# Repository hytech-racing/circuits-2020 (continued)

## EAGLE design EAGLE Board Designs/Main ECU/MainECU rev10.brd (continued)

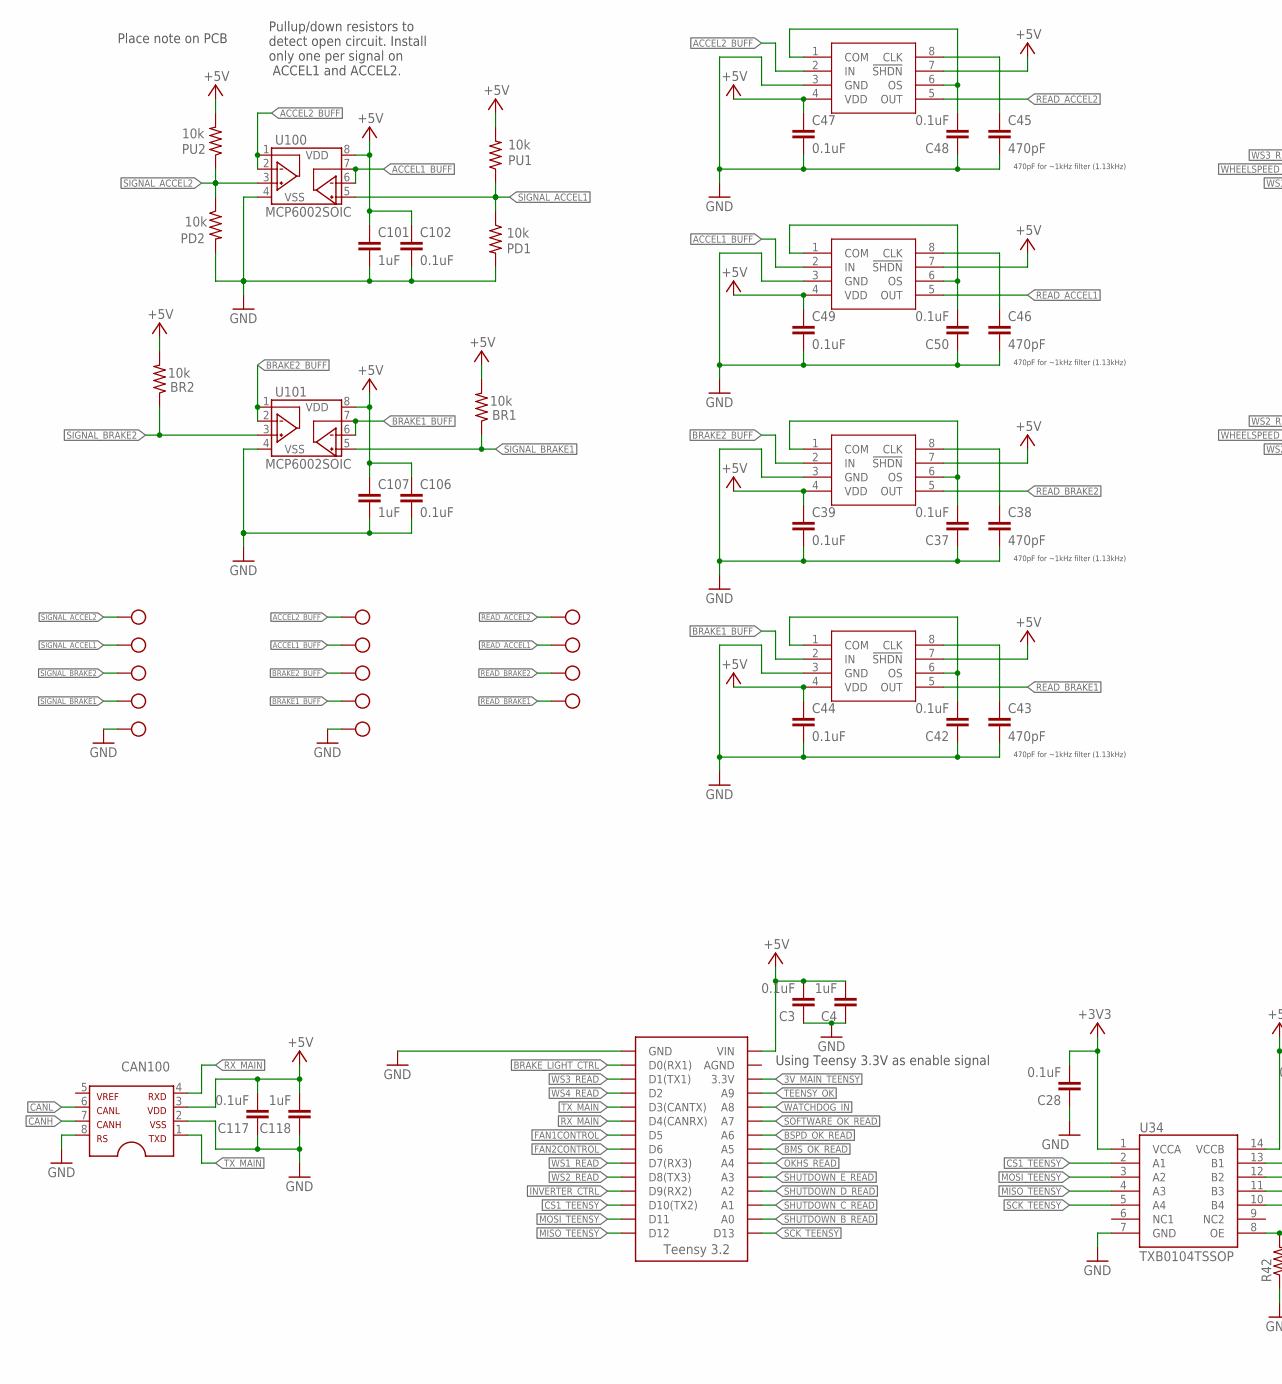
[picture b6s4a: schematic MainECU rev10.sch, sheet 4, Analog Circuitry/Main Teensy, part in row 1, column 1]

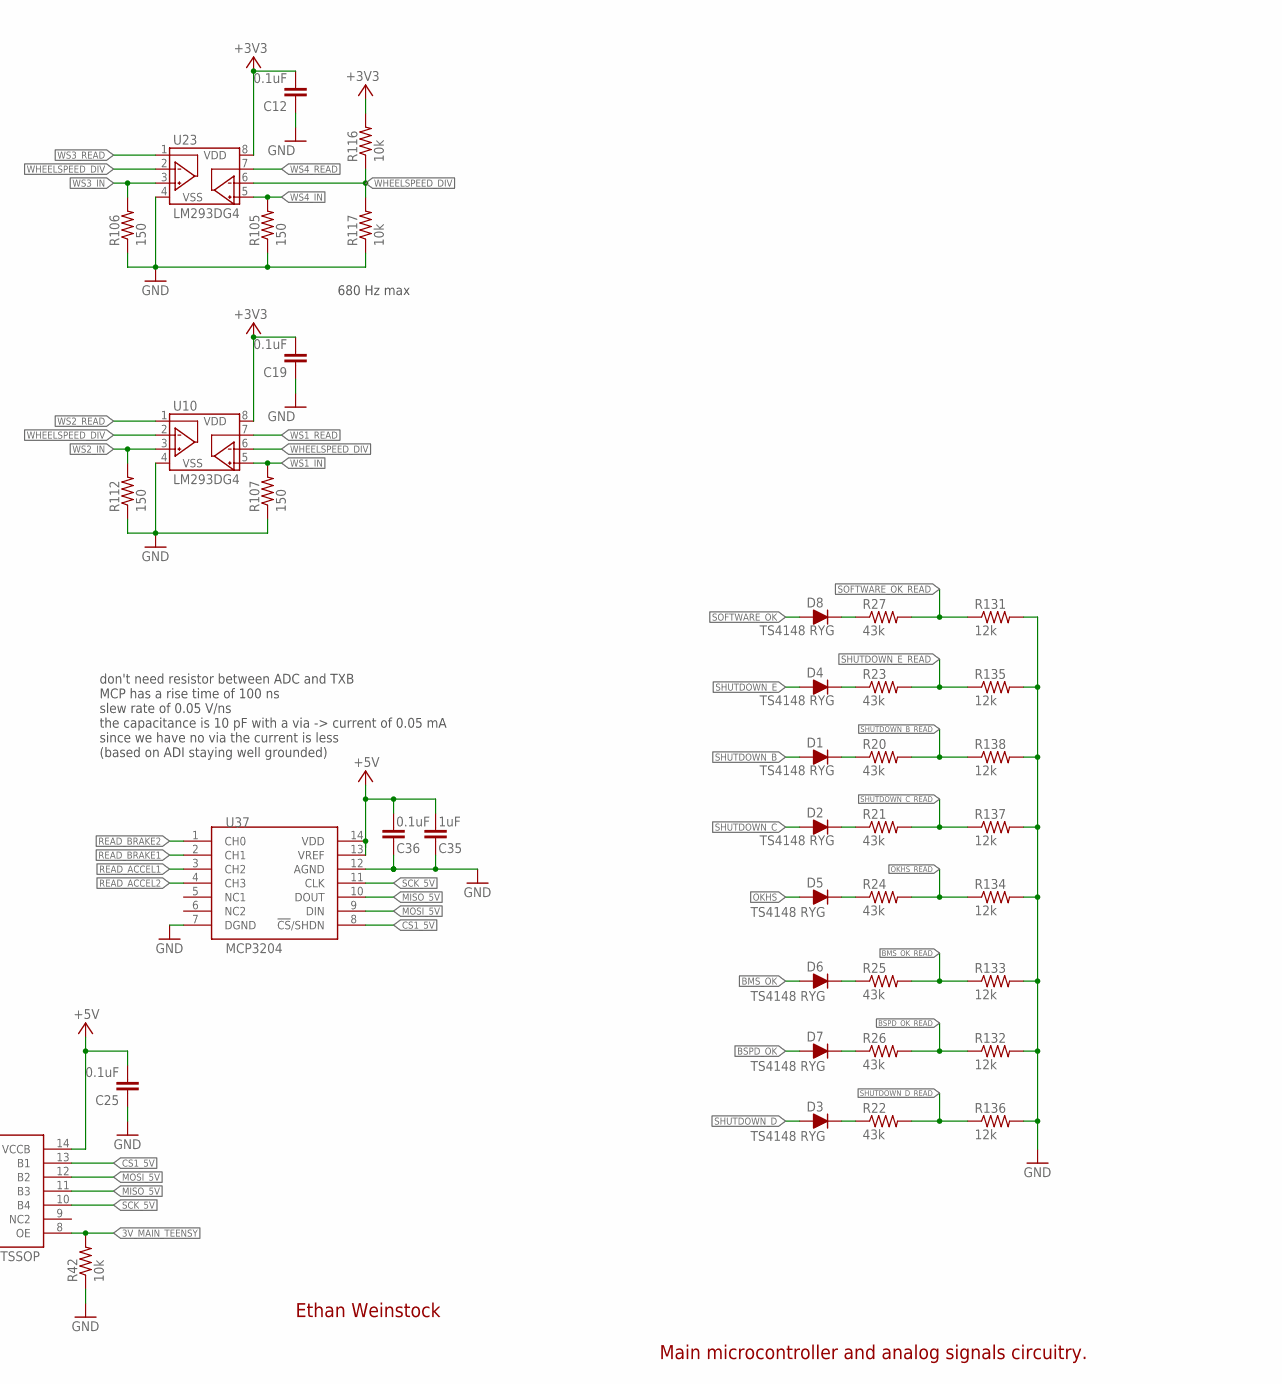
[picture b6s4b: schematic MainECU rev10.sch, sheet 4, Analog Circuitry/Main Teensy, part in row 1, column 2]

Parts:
ACCEL1_BUFF_TEST: 12V_TEST; MICRO_MINIATURE
ACCEL2_BUFF_TEST: TEST_POINTMICRO_MINIATURE; MICRO_MINIATURE
BR1, BR2: 10k; 0603-RES
BRAKE1_BUFF_TEST, BRAKE2_BUFF_TEST: TEST_POINTMICRO_MINIATURE; MICRO_MINIATURE
C3, C12, C19, C25, C28, C36, C37, C39, C42, C44, C47, C48, C49, C50, C102, C106, C117: 0.1uF; 0603-CAP
C4, C35, C101, C107, C118: 1uF; 0603-CAP
C38, C43, C45, C46: 470pF; 0603-CAP
CAN100: MCP2551; SOIC-08
D1, D2, D3, D4, D5, D6, D7, D8: TS4148 RYG; 0805_D
PD1, PD2: 10k; 0603-RES
PU1, PU2: 10k; 0603-RES
R20, R21, R22, R23, R24, R25, R26, R27: 43k; 0603-RES
R42, R116, R117: 10k; 0603-RES
R105, R106, R107, R112: 150; 0603-RES
R131, R132, R133, R134, R135, R136, R137, R138: 12k; 0603-RES
READ_ACCEL1_TEST: 12V_TEST; MICRO_MINIATURE
READ_ACCEL2_TEST: TEST_POINTMICRO_MINIATURE; MICRO_MINIATURE
READ_BRAKE1_TEST, READ_BRAKE2_TEST: TEST_POINTMICRO_MINIATURE; MICRO_MINIATURE
SIGNAL_ACCEL1_TEST: 12V_TEST; MICRO_MINIATURE
SIGNAL_ACCEL2_TEST: TEST_POINTMICRO_MINIATURE; MICRO_MINIATURE
SIGNAL_BRAKE1_TEST, SIGNAL_BRAKE2_TEST: TEST_POINTMICRO_MINIATURE; MICRO_MINIATURE
SIGNAL_GND: TEST_POINTMICRO_MINIATURE; MICRO_MINIATURE
U5: TEENSY_3.2_SIMPLE
U10, U23: LM293DG4; SOIC-08
U34: TXB0104TSSOP; TSSOP-14
U37: MCP3204; SO14
U38, U39, U44, U45: MAX7480; SOIC-08
U46: TEST_POINTMICRO_MINIATURE; MICRO_MINIATURE
U100, U101: MCP6002SOIC; SOIC-08

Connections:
3V_MAIN_TEENSY: R42.2, U5.3.3V, U34.8 (OE)
+3V3: C12.2, C19.2, C28.2, R116.2, U10.8 (VDD), U23.8 (VDD), U34.1 (VCCA); also elsewhere on the board
+5V: BR1.2, BR2.2, C3.2, C4.2, C25.2, C35.2, C36.2, C39.1, C44.1, C47.1, C49.1, C101.1, C102.1, C106.1, C107.1, C117.2, C118.2, CAN100.3, PU1.2, PU2.2, U5.VIN, U34.14 (VCCB), U37.13 (VREF), U37.14 (VDD), U38.4 (VDD), U38.7 (!SHDN), U39.4 (VDD), U39.7 (!SHDN), U44.4 (VDD), U44.7 (!SHDN), U45.4 (VDD), U45.7 (!SHDN), U100.8 (VDD), U101.8 (VDD); also elsewhere on the board
ACCEL1_BUFF: ACCEL2_BUFF_TEST.P$1, U45.2 (IN), U100.6 (VINB-), U100.7 (VOUTB)
ACCEL2_BUFF: ACCEL1_BUFF_TEST.P$1, U44.2 (IN), U100.1 (VOUTA), U100.2 (VINA-)
BMS_OK: D6.A; also elsewhere on the board
BMS_OK_READ: R25.2, R133.1, U5.A5
BRAKE1_BUFF: BRAKE2_BUFF_TEST.P$1, U39.2 (IN), U101.6 (VINB-), U101.7 (VOUTB)
BRAKE2_BUFF: BRAKE1_BUFF_TEST.P$1, U38.2 (IN), U101.1 (VOUTA), U101.2 (VINA-)
BRAKE_LIGHT_CTRL: U5.D0(RX1); also elsewhere on the board
BSPD_OK: D7.A; also elsewhere on the board
BSPD_OK_READ: R26.2, R132.1, U5.A6
CANH: CAN100.7; also elsewhere on the board
CANL: CAN100.6; also elsewhere on the board
CS1_5V: U34.13 (B1), U37.8 (!CS!/SHDN)
CS1_TEENSY: U5.D10(TX2), U34.2 (A1)
FAN1CONTROL: U5.D5; also elsewhere on the board
FAN2CONTROL: U5.D6; also elsewhere on the board
GND: C3.1, C4.1, C12.1, C19.1, C25.1, C28.1, C35.1, C36.1, C37.1, C38.2, C39.2, C42.1, C43.2, C44.2, C45.2, C46.2, C47.2, C48.1, C49.2, C50.1, C101.2, C102.2, C106.2, C107.2, C117.1, C118.1, CAN100.2, CAN100.8, PD1.2, PD2.2, R42.1, R105.1, R106.1, R107.1, R112.1, R117.1, R131.2, R132.2, R133.2, R134.2, R135.2, R136.2, R137.2, R138.2, SIGNAL_GND.P$1, U5.GND, U10.4 (VSS), U23.4 (VSS), U34.7 (GND), U37.7 (DGND), U37.12 (AGND), U38.3 (GND), U39.3 (GND), U44.3 (GND), U45.3 (GND), U46.P$1, U100.4 (VSS), U101.4 (VSS); also elsewhere on the board
INVERTER_CTRL: U5.D9(RX2); also elsewhere on the board
MISO_5V: U34.11 (B3), U37.10 (DOUT)
MISO_TEENSY: U5.D12, U34.4 (A3)
MOSI_5V: U34.12 (B2), U37.9 (DIN)
MOSI_TEENSY: U5.D11, U34.3 (A2)
unnamed: C43.1, U39.8 (CLK)
unnamed: C42.2, U39.1 (COM), U39.6 (OS)
unnamed: D4.C, R23.1
unnamed: D8.C, R27.1
unnamed: D5.C, R24.1
unnamed: D6.C, R25.1
unnamed: D3.C, R22.1
unnamed: D1.C, R20.1
unnamed: D2.C, R21.1
unnamed: D7.C, R26.1
unnamed: C45.1, U44.8 (CLK)
unnamed: C46.1, U45.8 (CLK)
unnamed: C48.2, U44.1 (COM), U44.6 (OS)
unnamed: C38.1, U38.8 (CLK)
unnamed: C37.2, U38.1 (COM), U38.6 (OS)
unnamed: C50.2, U45.1 (COM), U45.6 (OS)
OKHS: D5.A; also elsewhere on the board
OKHS_READ: R24.2, R134.1, U5.A4
READ_ACCEL1: READ_ACCEL2_TEST.P$1, U37.3 (CH2), U45.5 (OUT)
READ_ACCEL2: READ_ACCEL1_TEST.P$1, U37.4 (CH3), U44.5 (OUT)
READ_BRAKE1: READ_BRAKE2_TEST.P$1, U37.2 (CH1), U39.5 (OUT)
READ_BRAKE2: READ_BRAKE1_TEST.P$1, U37.1 (CH0), U38.5 (OUT)
RX_MAIN: CAN100.4, U5.D4(CANRX)
SCK_5V: U34.10 (B4), U37.11 (CLK)
SCK_TEENSY: U5.D13, U34.5 (A4)
SHUTDOWN_B: D1.A; also elsewhere on the board
SHUTDOWN_B_READ: R20.2, R138.1, U5.A0
SHUTDOWN_C: D2.A; also elsewhere on the board
SHUTDOWN_C_READ: R21.2, R137.1, U5.A1
SHUTDOWN_D: D3.A; also elsewhere on the board
SHUTDOWN_D_READ: R22.2, R136.1, U5.A2
SHUTDOWN_E: D4.A; also elsewhere on the board
SHUTDOWN_E_READ: R23.2, R135.1, U5.A3
SIGNAL_ACCEL1: PD1.1, PU1.1, SIGNAL_ACCEL2_TEST.P$1, U100.5 (VINB+); also elsewhere on the board
SIGNAL_ACCEL2: PD2.1, PU2.1, SIGNAL_ACCEL1_TEST.P$1, U100.3 (VINA+); also elsewhere on the board
SIGNAL_BRAKE1: BR1.1, SIGNAL_BRAKE2_TEST.P$1, U101.5 (VINB+); also elsewhere on the board
SIGNAL_BRAKE2: BR2.1, SIGNAL_BRAKE1_TEST.P$1, U101.3 (VINA+); also elsewhere on the board
SOFTWARE_OK: D8.A; also elsewhere on the board
SOFTWARE_OK_READ: R27.2, R131.1, U5.A7
TEENSY_OK: U5.A9; also elsewhere on the board
TX_MAIN: CAN100.1, U5.D3(CANTX)
WATCHDOG_IN: U5.A8; also elsewhere on the board
WHEELSPEED_DIV: R116.1, R117.2, U10.2 (VINA-), U10.6 (VINB-), U23.2 (VINA-), U23.6 (VINB-)
WS1_IN: R107.2, U10.5 (VINB+); also elsewhere on the board
WS1_READ: U5.D7(RX3), U10.7 (VOUTB)
WS2_IN: R112.2, U10.3 (VINA+); also elsewhere on the board
WS2_READ: U5.D8(TX3), U10.1 (VOUTA)
WS3_IN: R106.2, U23.3 (VINA+); also elsewhere on the board
WS3_READ: U5.D1(TX1), U23.1 (VOUTA)
WS4_IN: R105.2, U23.5 (VINB+); also elsewhere on the board
WS4_READ: U5.D2, U23.7 (VOUTB)

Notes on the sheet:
Pullup/down resistors to detect open circuit. Install only one per signal on ACCEL1 and ACCEL2.
470pF for ~1kHz filter (1.13kHz)
Ethan Weinstock
Main microcontroller and analog signals circuitry.
Place note on PCB
Using Teensy 3.3V as enable signal
680 Hz max
don't need resistor between ADC and TXB MCP has a rise time of 100 ns slew rate of 0.05 V/ns the capacitance is 10 pF with a via -> current of 0.05 mA since we have no via the current is less (based on ADI staying well grounded)

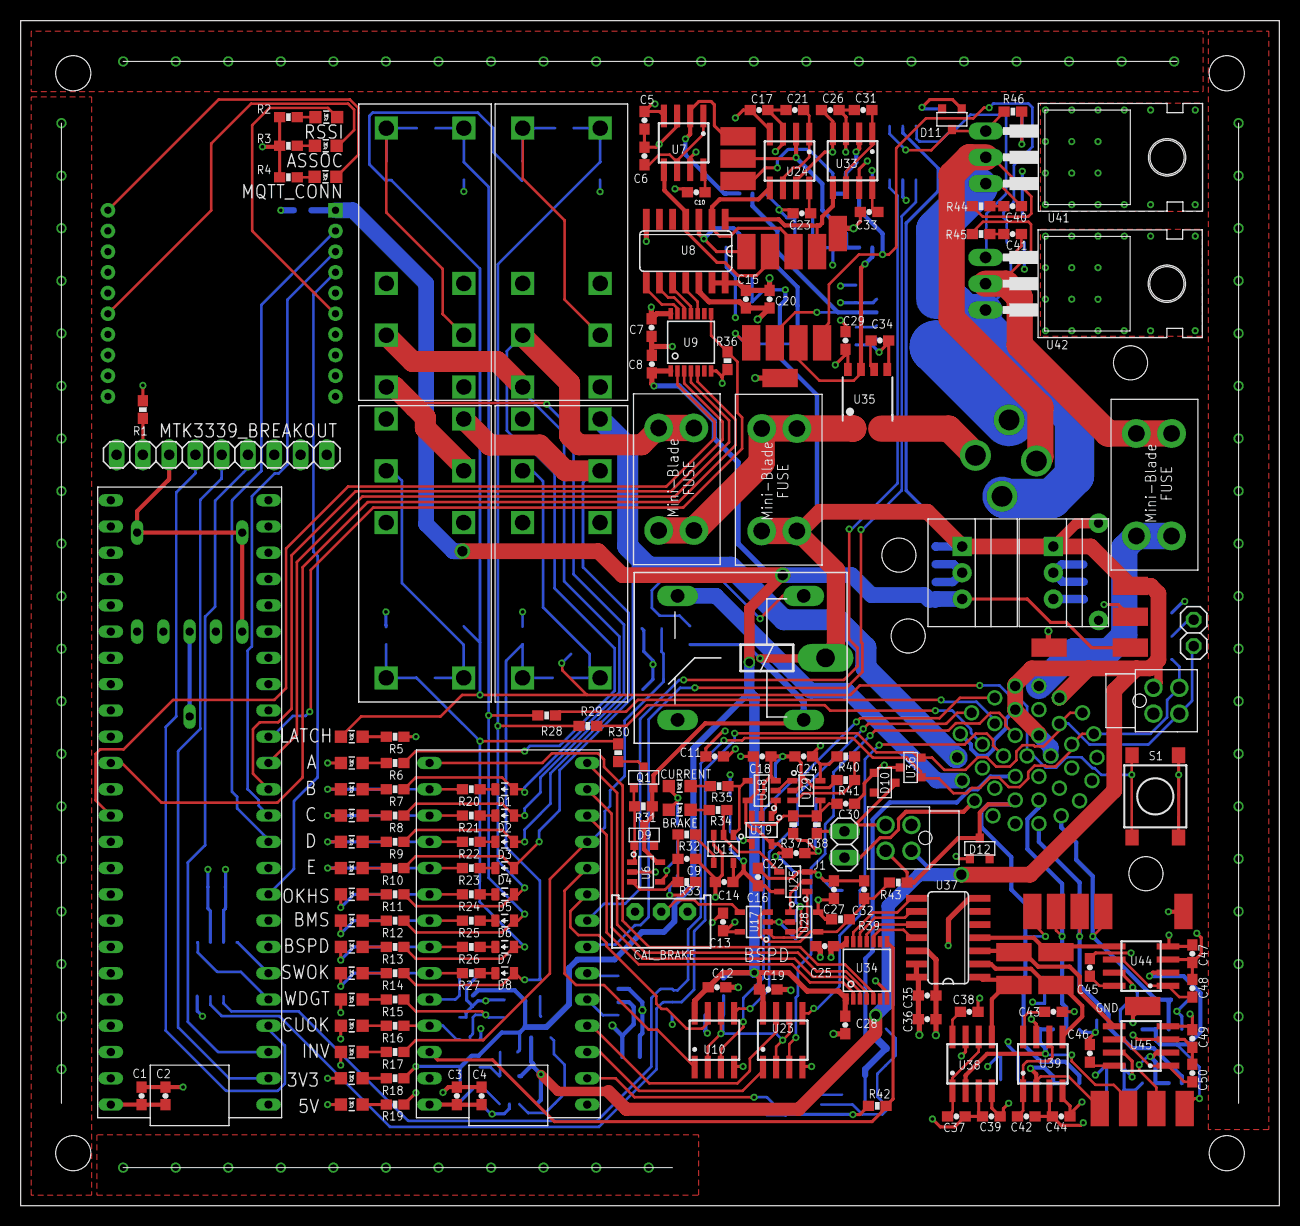
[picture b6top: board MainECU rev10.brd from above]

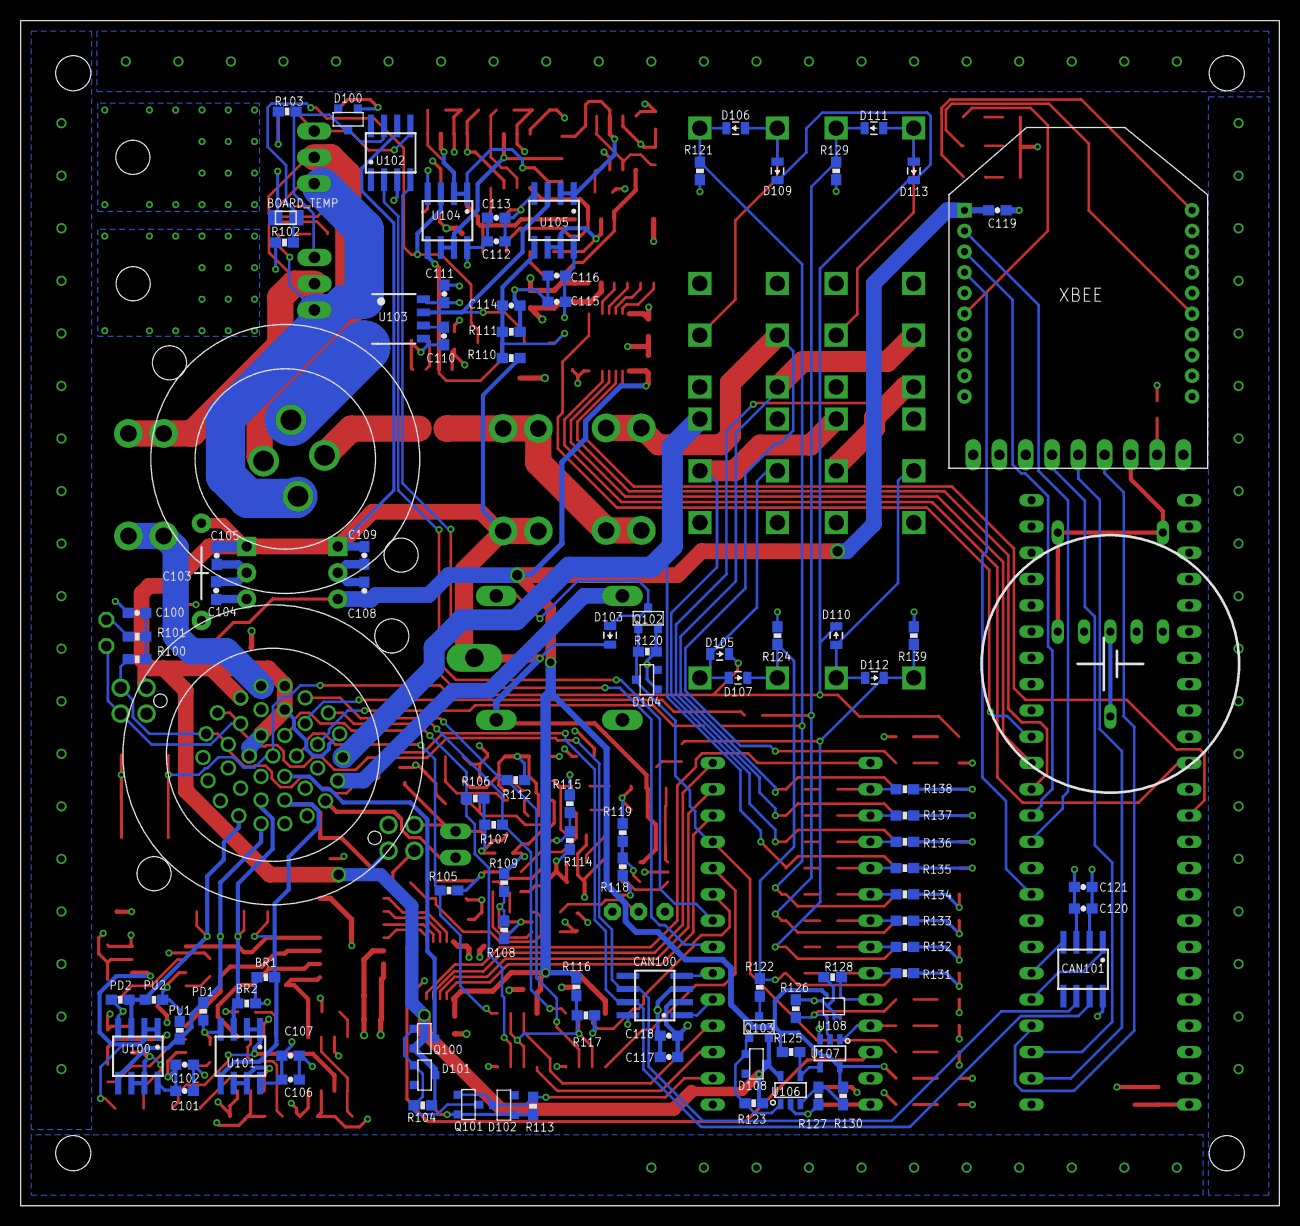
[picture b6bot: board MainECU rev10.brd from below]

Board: 4 copper layers, 121.7 x 114.6 mm, 310 parts (102 on the bottom side), 186 nets.

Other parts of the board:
U$1, U$2, U$3, U$4: M3_MOUNTING

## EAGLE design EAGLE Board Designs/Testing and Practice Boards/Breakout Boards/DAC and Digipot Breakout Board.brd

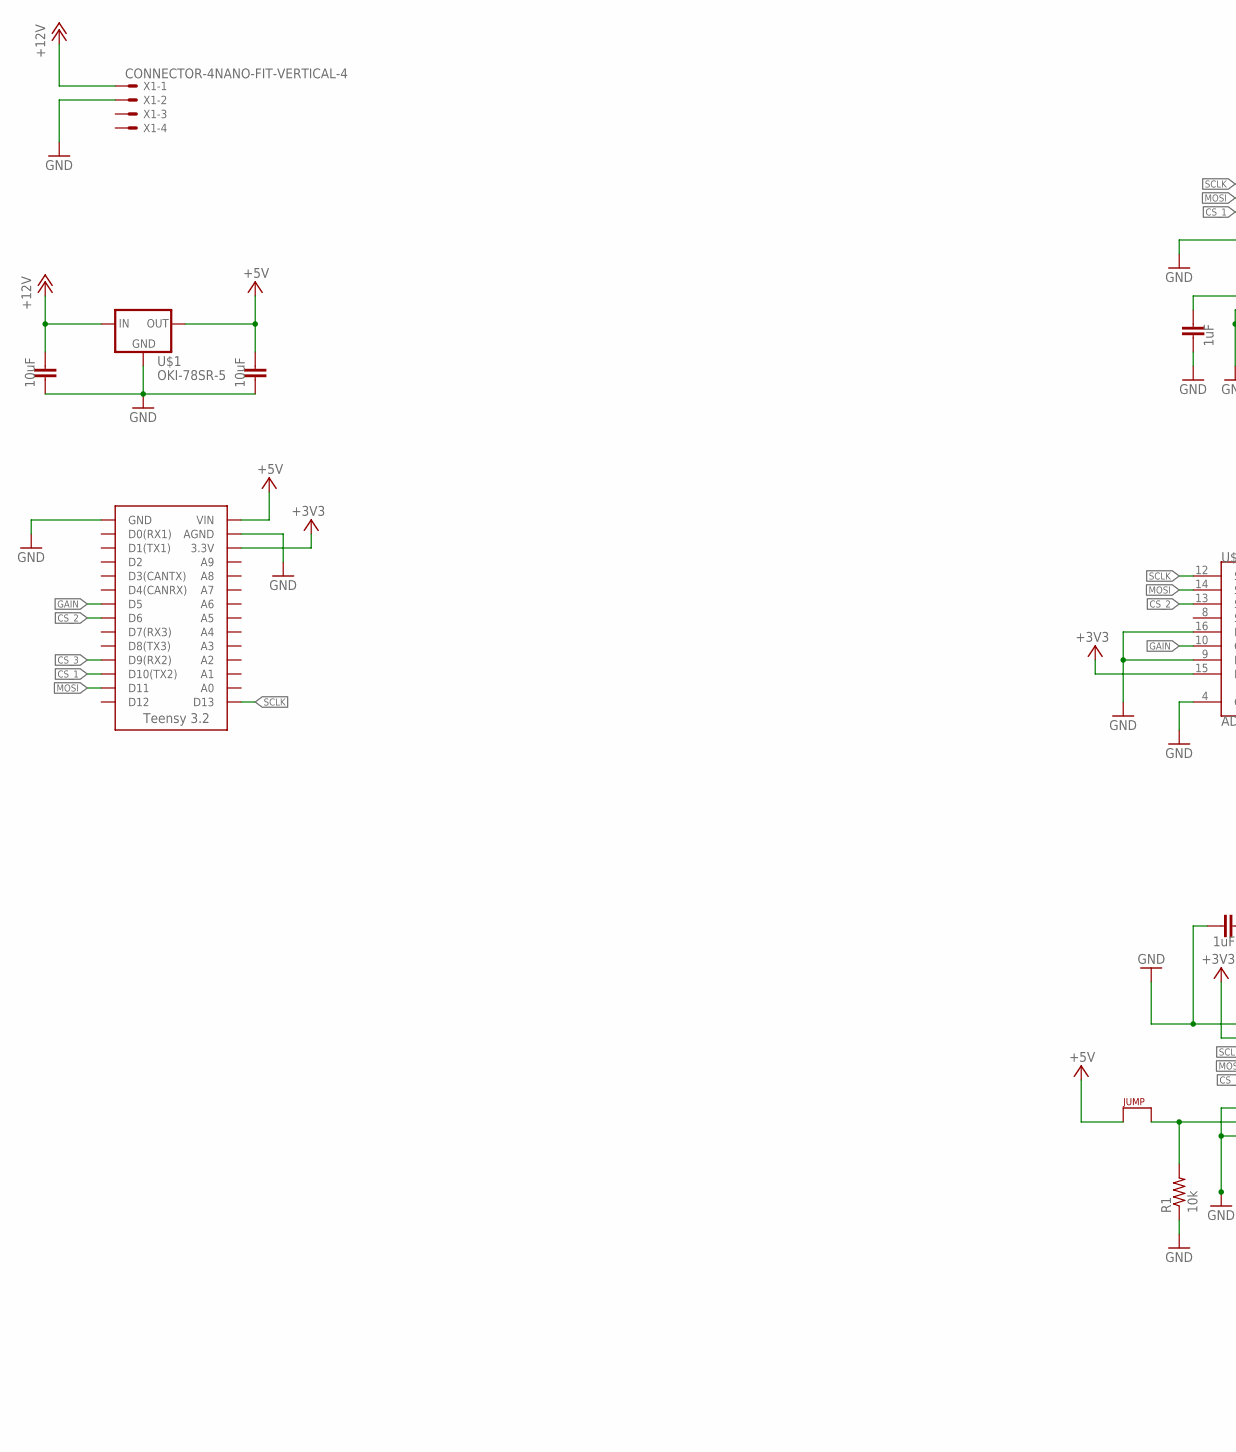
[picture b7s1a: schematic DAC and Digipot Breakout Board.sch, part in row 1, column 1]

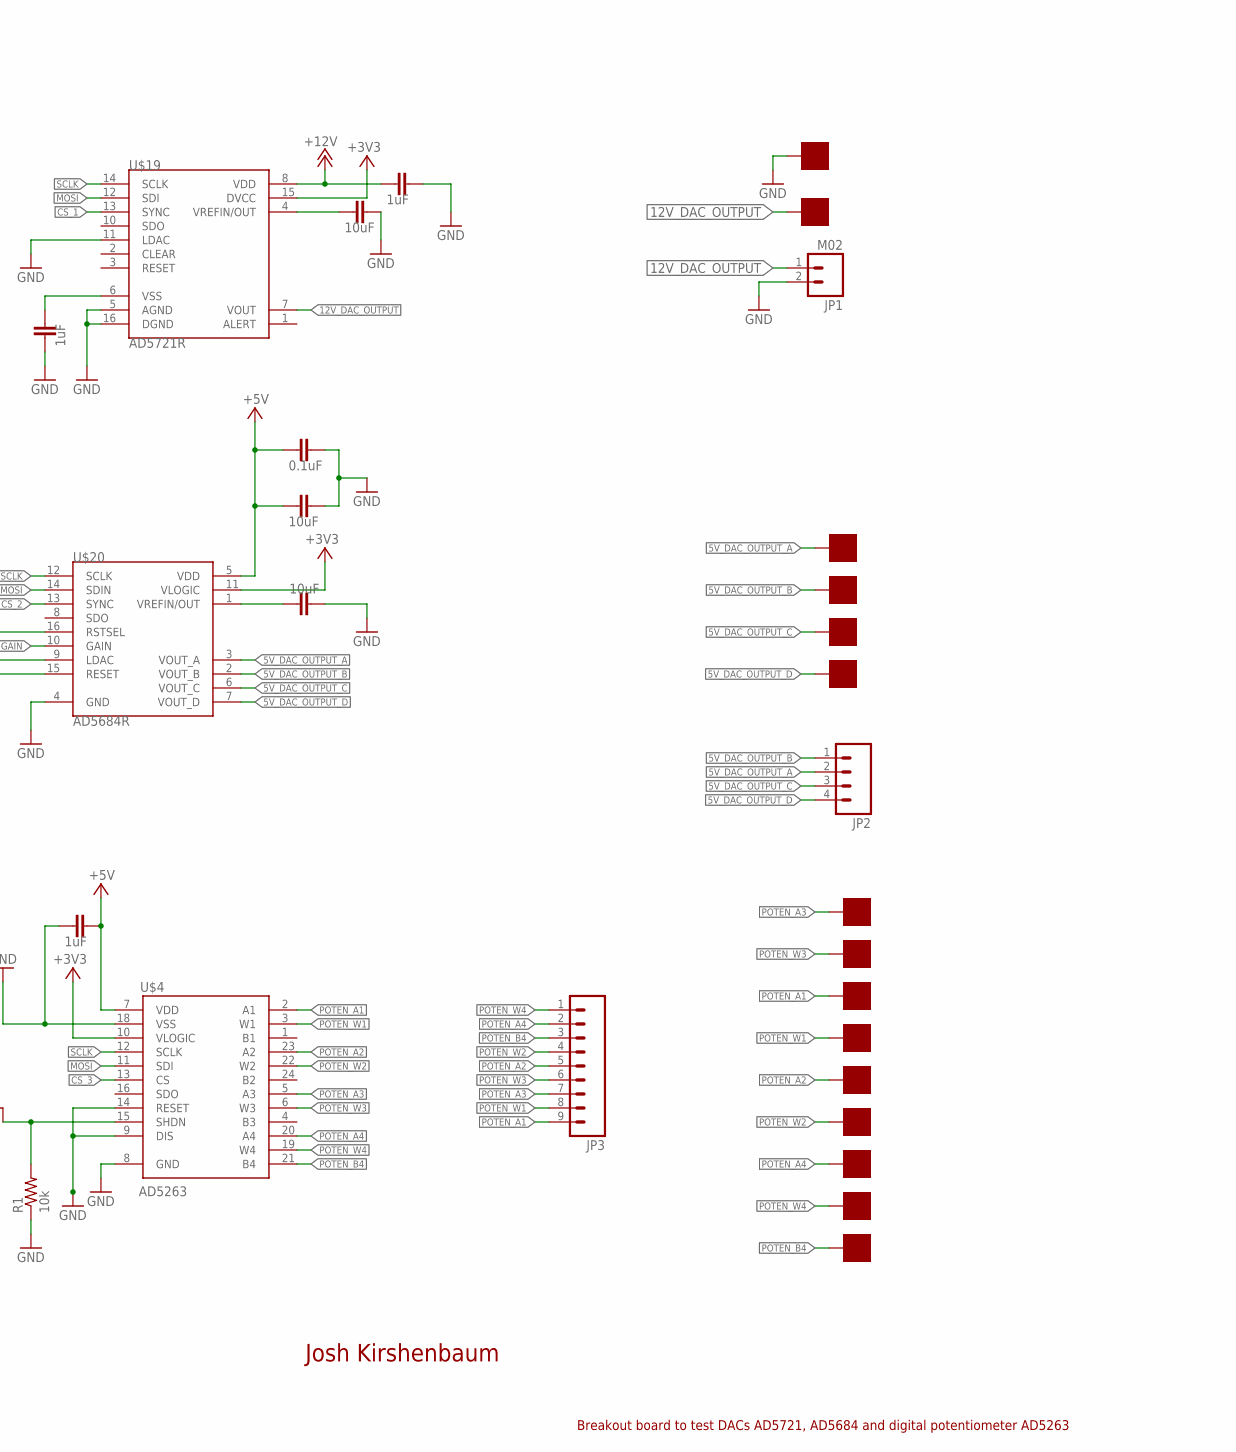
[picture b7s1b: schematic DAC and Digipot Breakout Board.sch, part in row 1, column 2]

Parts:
C1, C2, C5: 1uF; 0603-CAP
C3, C6, C7, C8, C9: 10uF; 0603-CAP
C4: 0.1uF; 0603-CAP
J1: JUMPER.1; 1X02
JP1: M02; 1X02
JP2: M04; 1X04
JP3: M09; 1X09
R1: 10k; 0603-RES
U$1: OKI-78SR-5; OKI-78SR
U$2: TEENSY_3.2_SIMPLE
U$4: AD5263; TSSOP-24
U$5, U$6, U$7, U$8, U$9, U$10, U$11, U$12, U$13, U$14, U$15, U$16, U$17, U$18, U$21: SOLDER_PAD; SOLDER_PAD_XSMALL
U$19: AD5721R; TSSOP-16
U$20: AD5684R; TSSOP-16
X1: CONNECTOR-4NANO-FIT-VERTICAL-4; NANO-FIT_VERTICAL-4

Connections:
5V_DAC_OUTPUT_A: JP2.2, U$6.P$1, U$20.3 (VOUT_A)
5V_DAC_OUTPUT_B: JP2.1, U$7.P$1, U$20.2 (VOUT_B)
5V_DAC_OUTPUT_C: JP2.3, U$8.P$1, U$20.6 (VOUT_C)
5V_DAC_OUTPUT_D: JP2.4, U$9.P$1, U$20.7 (VOUT_D)
12V_DAC_OUTPUT: JP1.1, U$5.P$1, U$19.7 (VOUT)
+3V3: U$2.3.3V, U$4.10 (VLOGIC), U$19.15 (DVCC), U$20.11 (VLOGIC), U$20.15 (RESET)
+5V: C3.2, C4.2, C5.1, C9.2, J1.1, U$1.3 (OUT), U$2.VIN, U$4.7 (VDD), U$20.5 (VDD)
+12V: C2.2, C8.2, U$1.1 (IN), U$19.8 (VDD), X1.P$1
CS_1: U$2.D10(TX2), U$19.13 (SYNC)
CS_2: U$2.D6, U$20.13 (SYNC)
CS_3: U$2.D9(RX2), U$4.13 (CS)
GAIN: U$2.D5, U$20.10 (GAIN)
GND: C1.2, C2.1, C3.1, C4.1, C5.2, C6.1, C7.2, C8.1, C9.1, JP1.2, R1.1, U$1.2 (GND), U$2.GND, U$4.8 (GND), U$4.9 (DIS), U$4.14 (RESET), U$4.18 (VSS), U$19.5 (AGND), U$19.11 (LDAC), U$19.16 (DGND), U$20.4 (GND), U$20.9 (LDAC), U$20.16 (RSTSEL), U$21.P$1, X1.P$2
MOSI: U$2.D11, U$4.11 (SDI), U$19.12 (SDI), U$20.14 (SDIN)
unnamed: J1.2, R1.2, U$4.15 (SHDN)
unnamed: C6.2, U$19.4 (VREFIN/OUT)
unnamed: C7.1, U$20.1 (VREFIN/OUT)
POTEN_A1: JP3.9, U$4.2 (A1), U$10.P$1
POTEN_A2: JP3.5, U$4.23 (A2), U$12.P$1
POTEN_A3: JP3.7, U$4.5 (A3), U$14.P$1
POTEN_A4: JP3.2, U$4.20 (A4), U$16.P$1
POTEN_B4: JP3.3, U$4.21 (B4), U$18.P$1
POTEN_W1: JP3.8, U$4.3 (W1), U$11.P$1
POTEN_W2: JP3.4, U$4.22 (W2), U$13.P$1
POTEN_W3: JP3.6, U$4.6 (W3), U$15.P$1
POTEN_W4: JP3.1, U$4.19 (W4), U$17.P$1
SCLK: U$2.D13, U$4.12 (SCLK), U$19.14 (SCLK), U$20.12 (SCLK)
VSS: C1.1, U$19.6 (VSS)

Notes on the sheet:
Josh Kirshenbaum
Breakout board to test DACs AD5721, AD5684 and digital potentiometer AD5263

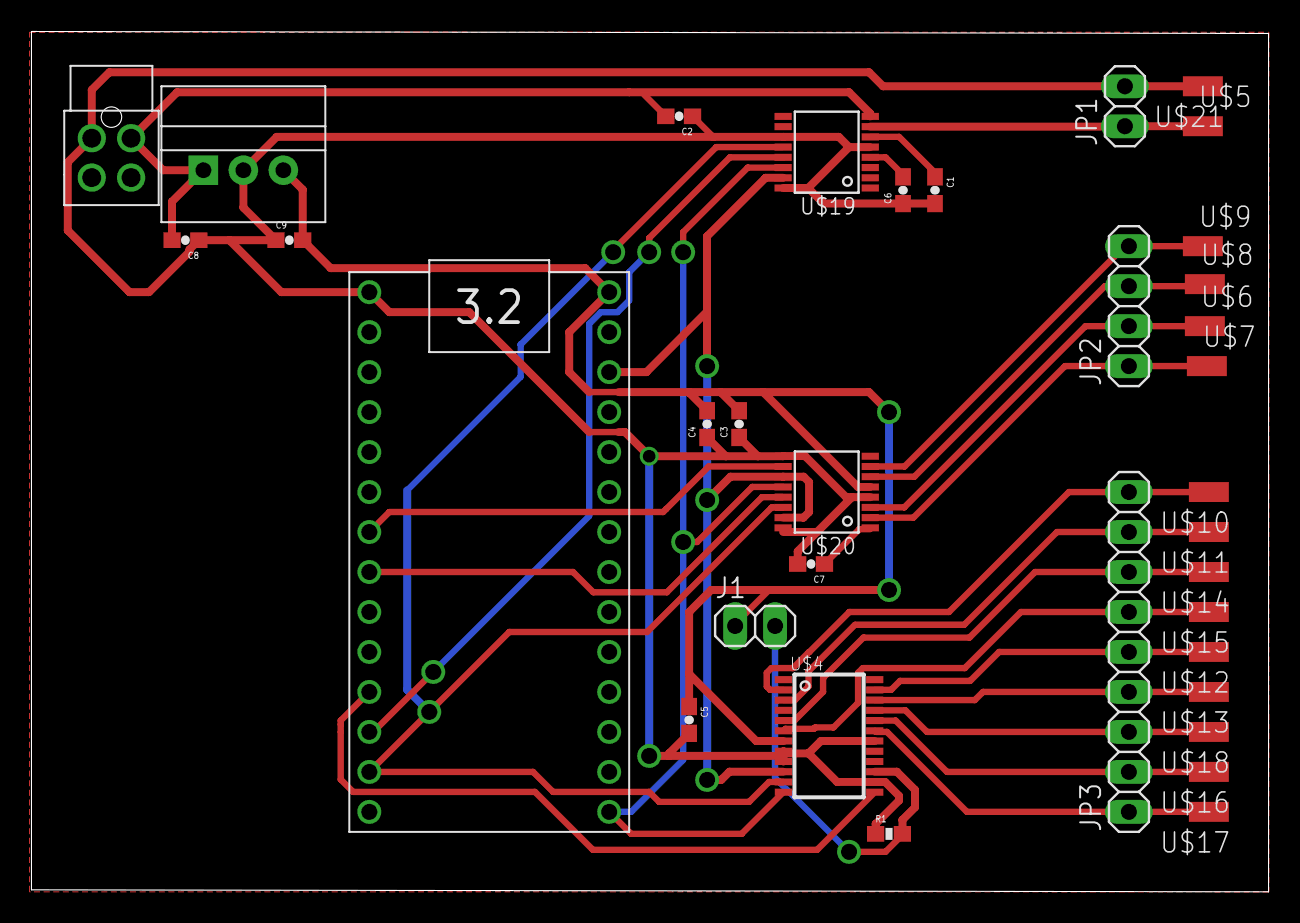
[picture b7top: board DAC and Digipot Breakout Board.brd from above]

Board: 2 copper layers, 78.6 x 54.7 mm, 35 parts (0 on the bottom side), 28 nets.

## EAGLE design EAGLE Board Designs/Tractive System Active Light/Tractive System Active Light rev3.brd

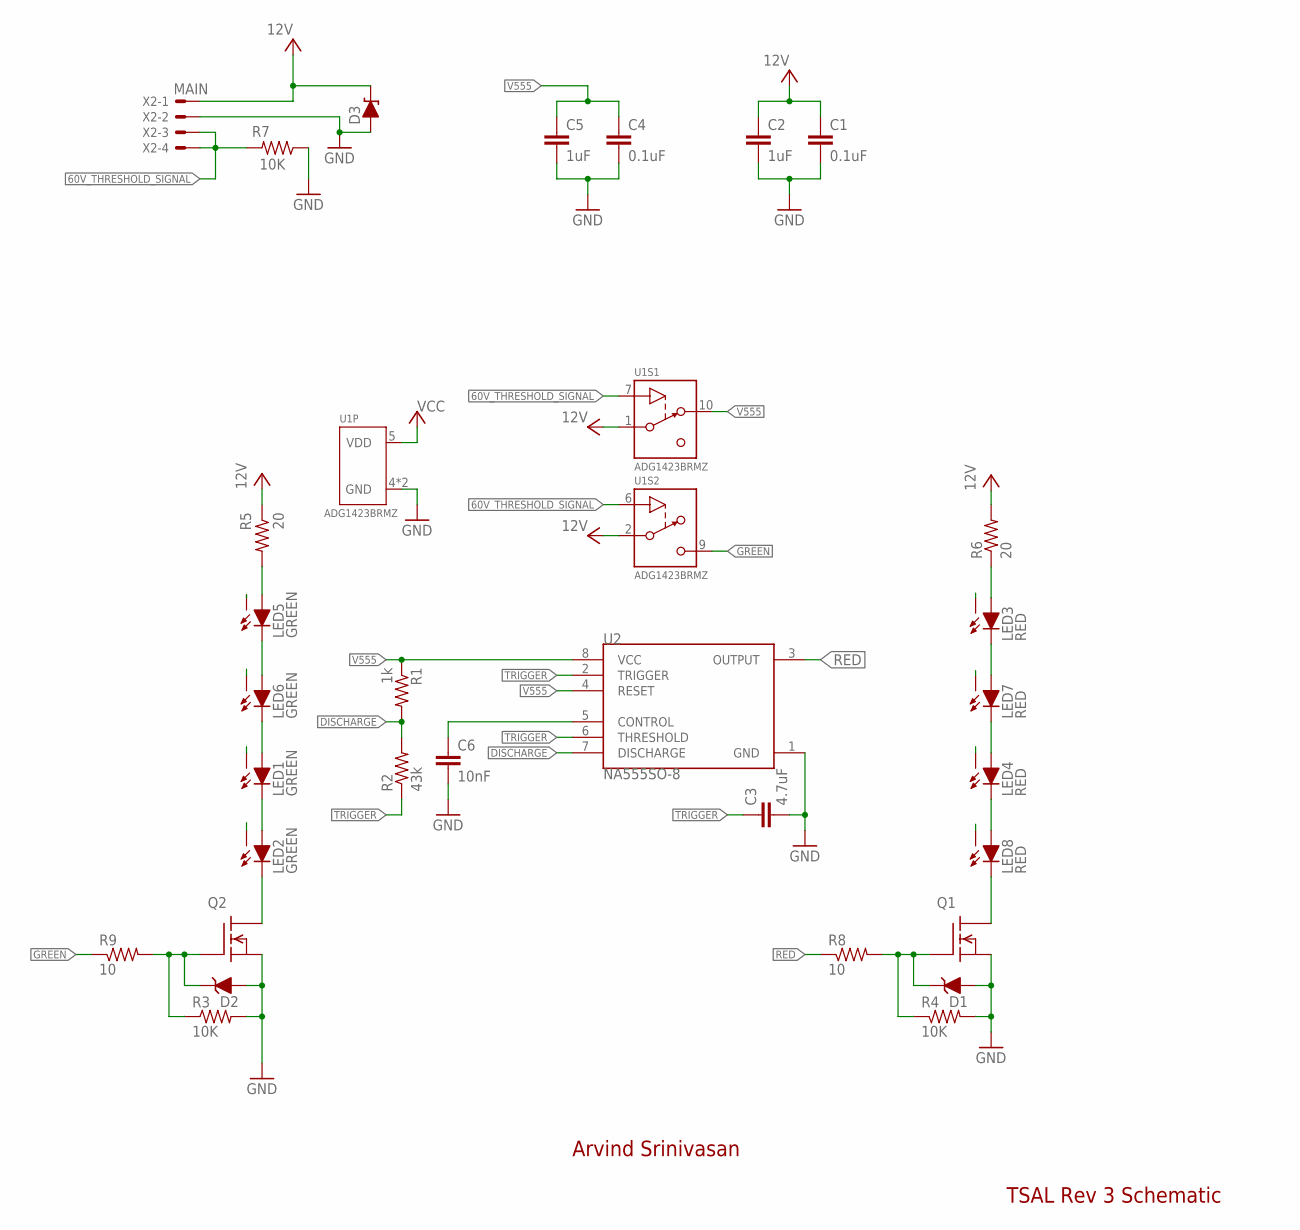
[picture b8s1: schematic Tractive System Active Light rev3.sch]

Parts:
C1, C4: 0.1uF; 0603-CAP; TOLERANCE 5%; VOLTAGE 25V
C2, C5: 1uF; 0603-CAP; TOLERANCE 5%; VOLTAGE 25V
C3: 4.7uF; 0603-CAP; TOLERANCE 5%; VOLTAGE 25V
C6: 10nF; 0603-CAP; TOLERANCE 5%; VOLTAGE 25V
D1, D2: MMBZ5246BLT1G; SOT23
D3: D15V0S1U2LP1608; U-DFN1608-2
LED1, LED2, LED5, LED6: GREEN; XP-E2
LED3, LED4, LED7, LED8: RED; XP-E2
Q1, Q2: DMG3406LSOT; SOT23
R1: 1k; 0603-RES; TOLERANCE 1%
R2: 43k; 0603-RES; TOLERANCE 1%
R3, R4, R7: 10K; 0603-RES; TOLERANCE 1%
R5, R6: 20; 0603-RES; TOLERANCE 1%
R8, R9: 10; 0603-RES; TOLERANCE 1%
U1: ADG1423; MSOP-10
U2: NA555SO-8; SOIC-08
X2: MAIN; NANO-FIT_RIGHT_ANGLE-4-SURFACE

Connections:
60V_THRESHOLD_SIGNAL: R7.2, U1.6 (IN), U1.7 (IN), X2.3, X2.4
DISCHARGE: R1.2, R2.2, U2.7 (DISCHARGE)
GND: C1.2, C2.2, C3.2, C4.2, C5.2, C6.2, D1.1 (A), D2.1 (A), D3.P$1 (A), Q1.2 (S), Q2.2 (S), R3.2, R4.2, R7.1, U1.4 (GND), U1.8 (GND), U2.1 (GND), X2.2
GREEN: R9.1, U1.9 (D)
unnamed: LED1.A, LED6.C
unnamed: LED2.C, Q2.3 (D)
unnamed: LED5.C, LED6.A
unnamed: D1.3 (C), Q1.1 (G), R4.1, R8.2
unnamed: LED5.A, R5.2
unnamed: D2.3 (C), Q2.1 (G), R3.1, R9.2
unnamed: LED8.C, Q1.3 (D)
unnamed: LED3.A, R6.1
unnamed: C6.1, U2.5 (CONTROL)
unnamed: LED1.C, LED2.A
unnamed: LED3.C, LED7.A
unnamed: LED4.A, LED7.C
unnamed: LED4.C, LED8.A
RED: R8.1, U2.3 (OUTPUT)
THERM: LED1.X, LED2.X, LED3.X, LED4.X, LED5.X, LED6.X, LED7.X, LED8.X
TRIGGER: C3.1, R2.1, U2.2 (TRIGGER), U2.6 (THRESHOLD)
V555: C4.1, C5.1, R1.1, U1.10 (D), U2.4 (RESET), U2.8 (VCC)
VCC: C1.1, C2.1, D3.P$2 (C), R5.1, R6.2, U1.1 (S), U1.2 (S), U1.5 (VDD), X2.1

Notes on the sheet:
Arvind Srinivasan
TSAL Rev 3 Schematic

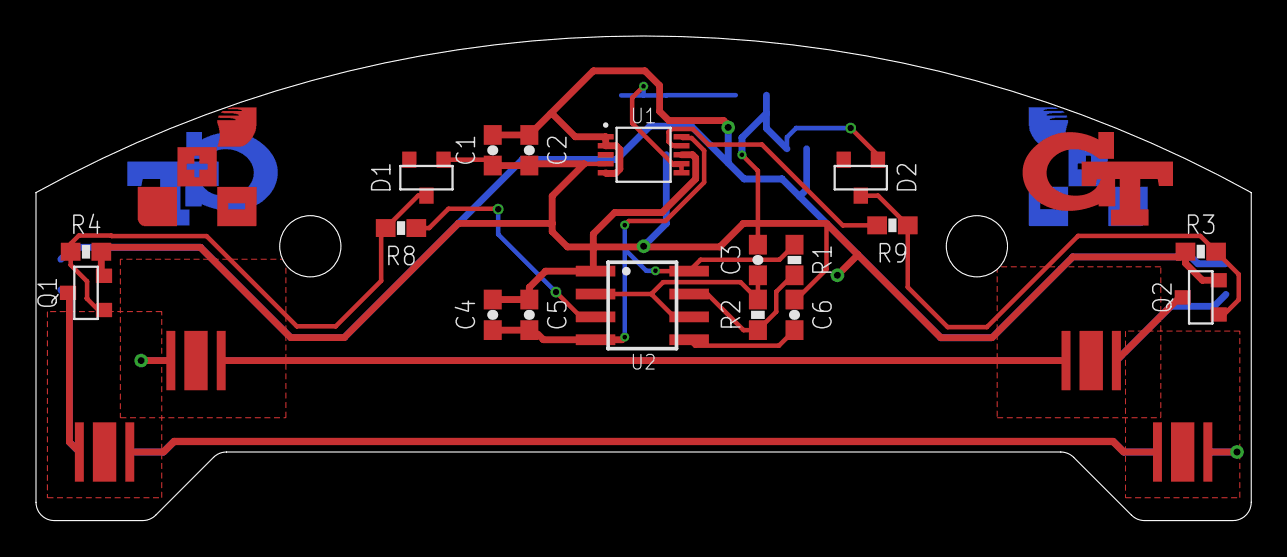
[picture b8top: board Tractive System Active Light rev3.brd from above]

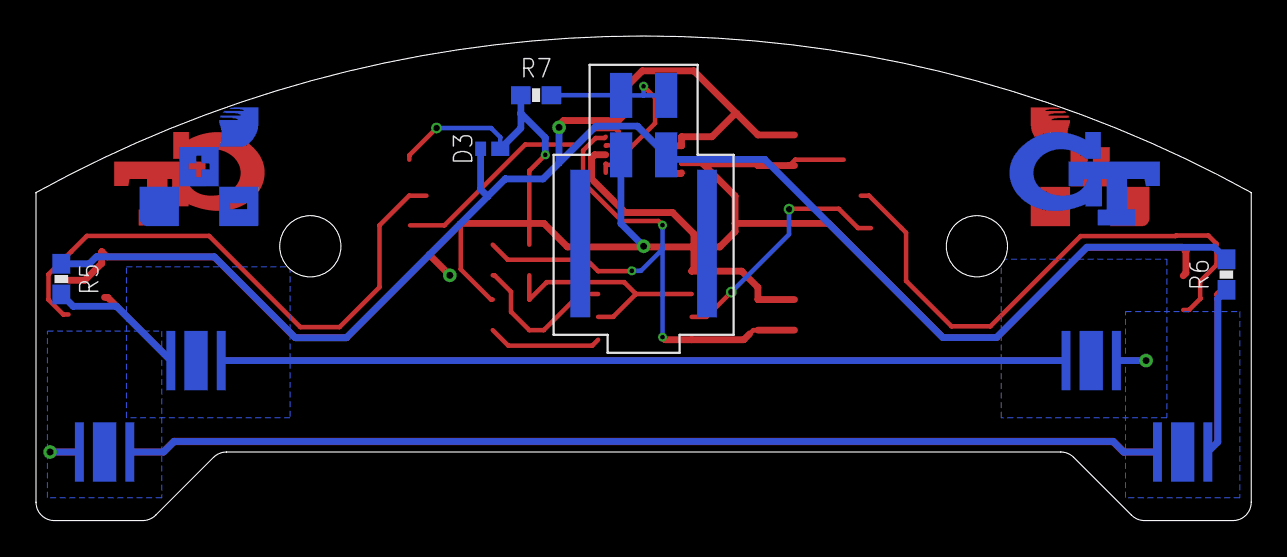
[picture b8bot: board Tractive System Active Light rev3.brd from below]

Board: 2 copper layers, 67.5 x 26.9 mm, 33 parts (9 on the bottom side), 22 nets.

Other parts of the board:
$$U$1: M3_MOUNTING
U$2: M3_MOUNTING
